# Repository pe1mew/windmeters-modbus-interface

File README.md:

# Windmeters Modbus Interface

A CH32V003-based interface board that bridges classic analog wind sensors —
a **cup anemometer** (reed-relay pulses) and a **wind-vane potentiometer**
(0–360°) — onto **Modbus RTU over RS-485**, powered by 24 V passive PoE and
designed for daisy-chained field buses.

One PCB serves both sensor types; the firmware build selects the variant.
Each variant responds at its own Modbus address, selected by a solder
jumper:

| Variant | Jumper open | Jumper bridged |
|---|---|---|
| Wind speed (`wind_speed`) | **30** | 35 |
| Wind direction (`wind_direction`) | **31** | 36 |
| Both, one slave (`wind_combined`) | **32** | 37 |

The `wind_combined` build serves both sensors through a single Modbus
address; its register map carries speed and direction at their own
register addresses, with the direction raw-ADC diagnostic at 30013 (30005
holds the speed pulse count).

## Project status (2026-07)

| Area | State |
|---|---|
| Requirements | [`design/TDS.md`](design/TDS.md) **v0.9** — 69 active requirements (incl. FR-S39 persistence, FR-S40 runtime calibration) + §4 as-built hardware from the KiCad PCB, hardened by multi-agent audits + verification passes |
| Drivers | Pulse counting, ADC/circular-mean, Modbus RTU — all HIL-verified on silicon ([`design/driverDevelopment.md`](design/driverDevelopment.md)) |
| Product firmware | Integration stages A–F complete; **TDS-functionally complete** on all three variants (speed, direction, combined), acceptance suite green ([`design/integrationPlan.md`](design/integrationPlan.md)) |
| Hardware/HIL | KiCad schematic/PCB in design; **§9.1 MAX3485-rig HIL complete on all three variants**; real-PCB rows (§9.2) pending |
| Release | Firmware version 1 not yet tagged ([`software/firmware/RELEASES.md`](software/firmware/RELEASES.md)) |

## Hardware

- **MCU**: WCH CH32V003J4M6 (RISC-V, SOP-8, 16 KB flash / 2 KB RAM) — the
  8-pin package drives the whole design: single-wire UART discipline,
  remap tricks, and a zero-interrupt firmware architecture
  ([`design/softwareArchitecture.md`](design/softwareArchitecture.md)).
- **RS-485**: MAX3485; DI+RO tied to PD6, DE+R̄Ē tied to PC2 with a 10 k
  pull-down (keeps the bus safe during reset/flashing); 120 Ω terminator
  behind a solder jumper; A/B fail-safe bias; SM712 TVS.
- **Power**: 24 V passive PoE on the spare pairs (4/5 = +, 7/8 = −) →
  DB207 bridge (polarity protection only) → HLK-K7803 buck → 3.3 V.
- **Connectors**: 2× RJ45 for the daisy-chained bus, two RJ14 sensor jacks
  (anemometer + wind direction), 3-pin header for the WCH-LinkE programmer
  (SWIO on PD1).

## Modbus register map (summary)

12 input registers (FC04) and 6 holding registers (FC03/06/16); registers
of an absent sensor read 0, and the combined build adds a 13th input
register (30013, direction raw ADC). Highlights: instantaneous and averaged
values, status bits, identification (build + firmware version), uptime,
CRC/served counters, gust, seconds-since-last-pulse.
**6** holding registers: direction offset, measurement window, averaging
window, low-speed cut-off, and the anemometer calibration (factor C +
pulses-per-rotation, FR-S40 — so one image serves any anemometer, set over
Modbus). All **persisted in flash across reset/power-loss** (FR-S39); the §2.8
defaults apply only on first boot / erased store. The authoritative map with
ranges, defaults, and requirement IDs is [`design/TDS.md`](design/TDS.md)
§2.7/§2.8.

## Repository layout

| Path | Contents |
|---|---|
| [`design/`](design/README.md) | The design-document chain (index in [`design/README.md`](design/README.md)): scratchBook → TDS → softwareArchitecture (+ UML diagrams in `design/diagrams/`) → driverDevelopment → integrationPlan |
| `hardware/KiCad/` | Schematic + PCB (KiCad); symbol libraries as git submodules |
| `hardware/Documentation/` | Component datasheets (HLK-K78xx, DB20x, Kradex enclosure, …) |
| `software/firmware/` | Product firmware (PlatformIO + ch32v003fun), three build envs (speed / direction / combined) + `_test` variants |
| `software/drivers/` | Standalone driver projects with HIL test shells (the verified libraries the product references in place) |
| `software/hil/` | Scripted hardware-in-the-loop harness: Saleae Logic 2 (MCP) + ADALM2000 (libm2k) + `acceptance/` pytest suite; consolidated [`testReport.md`](software/hil/testReport.md) |
| `Doxyfile` | Doxygen config — builds a single site (design docs + API reference) with this README as the landing page |
| `documentation/` | Chip pinout and project reference images |

Clone with submodules:

```sh
git clone --recurse-submodules https://github.com/pe1mew/windmeters-modbus-interface.git
```

## Building and flashing

Requires [PlatformIO](https://platformio.org/) and a WCH-LinkE on SWIO.

```sh
cd software/firmware
pio run -e wind_speed              # or wind_direction, or wind_combined
pio run -e wind_speed -t upload    # flash via WCH-LinkE
```

Resource ceilings (14 336 B flash / 1 792 B RAM, NFR-RES01) are enforced as
hard build gates. `*_test` environments add bench-only hooks — never
release those binaries. The firmware version byte lives in
`src/version.h`; the release process is documented in `RELEASES.md`.

## Testing

- **Host tests** (no hardware): the circular-mean math is exhaustively
  verified in Python — `python software/drivers/common/circmean/test_circmean.py`.
- **Acceptance suite** (bench: Saleae Logic 2 with its MCP server, ADALM2000,
  WCH-LinkE, TTL Modbus rig):

  ```sh
  cd software/hil/acceptance
  ..\.venv-m2k\Scripts\python.exe -m pytest . --build speed
  ```

  One command per flashed variant; covers the register map, protocol
  vectors, measurement services, averaging engine, version chain, and
  build gates. See [`software/hil/README.md`](software/hil/README.md) for
  instrument setup, wiring, and the bench-quirk catalogue.
- **HIL test report** — [`software/hil/testReport.md`](software/hil/testReport.md)
  consolidates every hardware-in-the-loop test (driver-phase, integration-
  stage, and MAX3485 transceiver rig) with its setup, expected result, and
  pass/fail verdict in one place.

## Documentation

- **Design record** — [`design/README.md`](design/README.md) indexes the
  document chain (requirements → architecture → drivers → integration) and
  the UML diagrams.
- **API + design site** — the firmware headers/sources carry full Doxygen,
  and [`Doxyfile`](Doxyfile) folds the design docs in as pages with this
  README as the landing page. Build the browsable HTML with:

  ```sh
  doxygen Doxyfile        # output in documentation/doxygen/html/index.html
  ```
- **Test evidence** — [`software/hil/testReport.md`](software/hil/testReport.md)
  is the consolidated hardware-in-the-loop test report.

## Related repositories

- [`pe1mew/windmeters-modbus-interface-tester`](https://github.com/pe1mew/windmeters-modbus-interface-tester) —
  the Modbus RTU master bench tool (M5Stack AtomS3 + RS-485) used to
  exercise this device; its bench findings seeded this project's TDS.

## License

Software is provided under a Source-Available Non-Commercial License;
documentation and images under CC BY-NC-ND 4.0. See [LICENSE](LICENSE) and
[license.md](license.md). Third-party datasheets and KiCad library
submodules remain under their owners' terms.

## Author

Remko Welling (PE1MEW)

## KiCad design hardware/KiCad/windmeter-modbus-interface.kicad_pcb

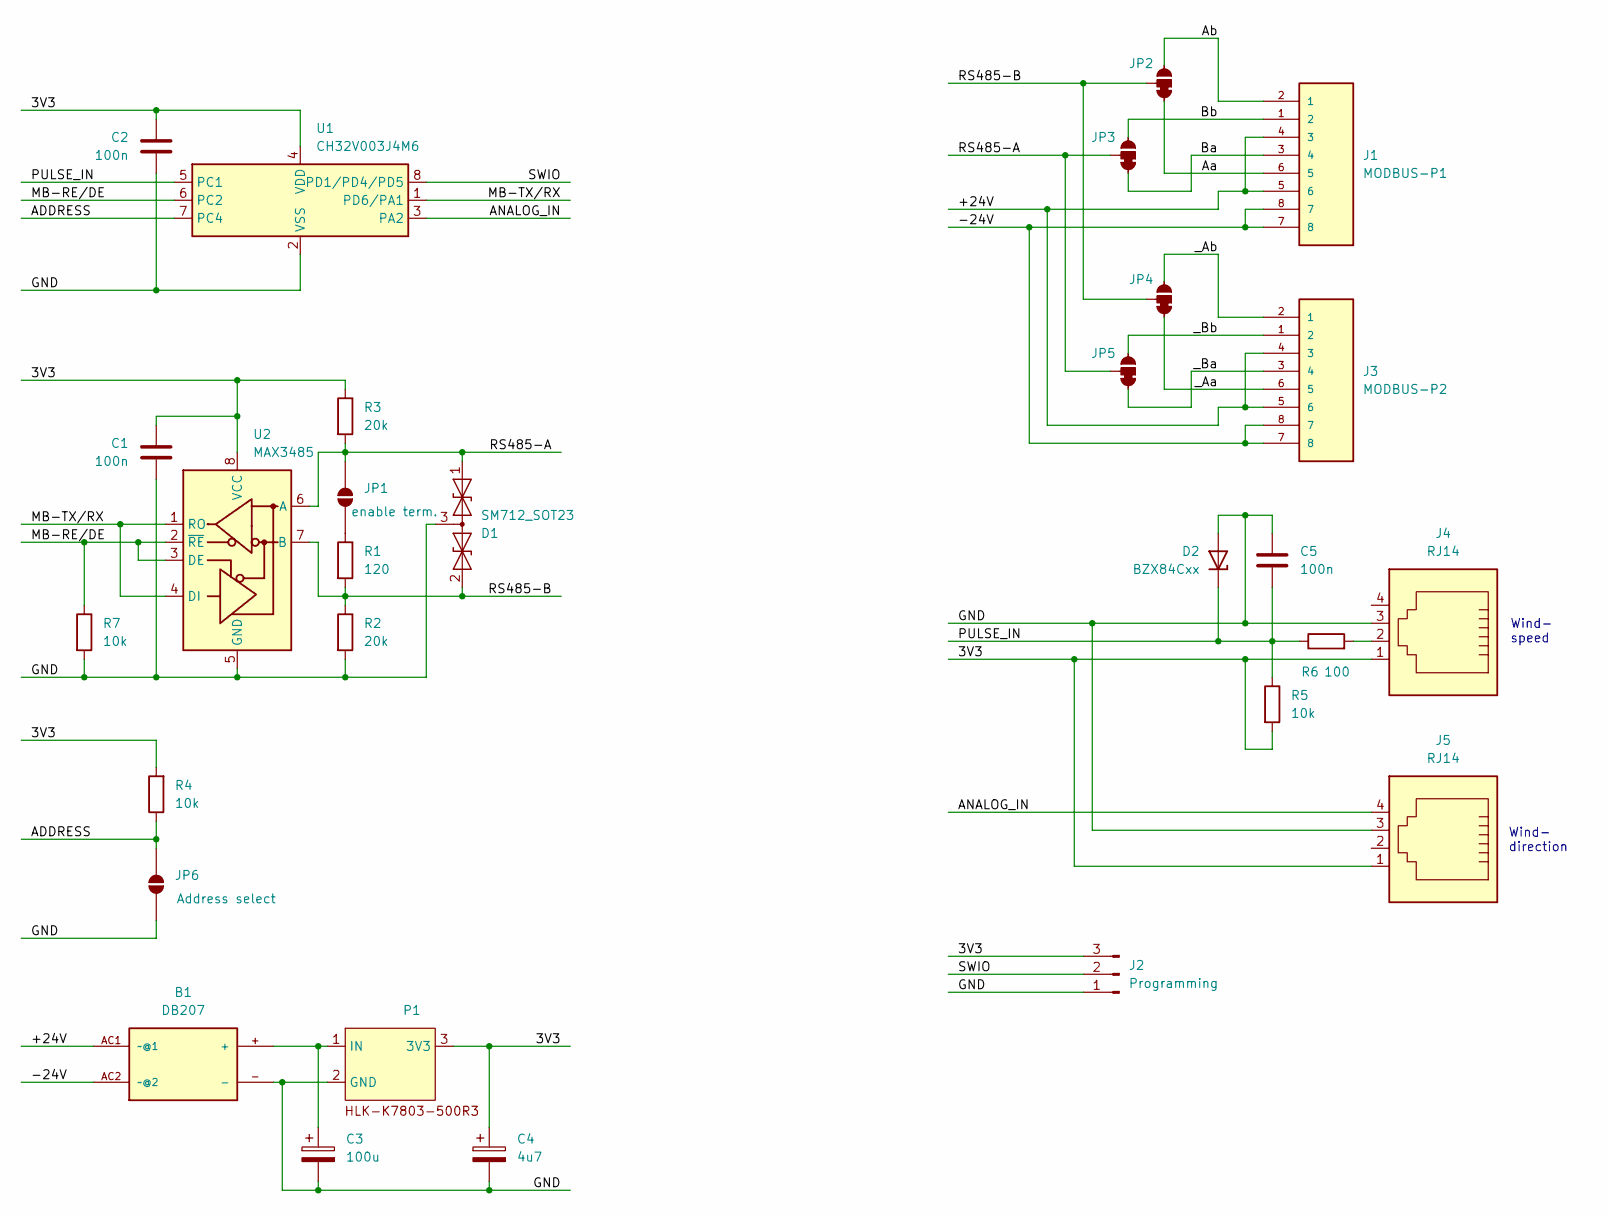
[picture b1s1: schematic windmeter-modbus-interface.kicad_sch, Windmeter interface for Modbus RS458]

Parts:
B1: DB207; DB207-DIP-4
C1, C2, C5: 100n; C_1206_3216Metric_Pad1.33x1.80mm_HandSolder
C3: 100u; CP_Radial_D8.0mm_P5.00mm
C4: 4u7; CP_Radial_D5.0mm_P2.50mm
D1: SM712_SOT23; SOT-23
D2: BZX84Cxx; SOT-23
J1: MODBUS-P1; CONN_215877-1; PARTREV AF1
J2: Programming; PinHeader_1x03_P2.54mm_Vertical
J3: MODBUS-P2; CONN_215877-1; PARTREV AF1
J4, J5: RJ14; RJ14_Connfly_DS1133-S4_Horizontal
JP1: enable term.; SolderJumper-2_P1.3mm_Open_Pad1.0x1.5mm
JP2, JP3, JP4, JP5: SolderJumper-3_P1.3mm_Bridged12_Pad1.0x1.5mm_NumberLabels
JP6: Address select; SolderJumper-2_P1.3mm_Open_Pad1.0x1.5mm
P1: HLK-K7803-500R3
R1: 120; R_1206_3216Metric_Pad1.30x1.75mm_HandSolder
R2, R3: 20k; R_1206_3216Metric_Pad1.30x1.75mm_HandSolder
R4, R5, R7: 10k; R_1206_3216Metric_Pad1.30x1.75mm_HandSolder
R6: 100; R_1206_3216Metric_Pad1.30x1.75mm_HandSolder
U1: CH32V003J4M6; JEITA_SOIC-8_3.9x4.9mm_P1.27mm
U2: MAX3485; SOIC-8_3.9x4.9mm_P1.27mm

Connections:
/3V3: C1.1, C2.1, C4.1, J2.3, J4.1, J5.1, P1.3 (3V3), R3.1, R4.2, R5.2, U1.4 (VDD), U2.8 (VCC)
/+24V: B1.AC1 (~@1), J1.4 (3), J1.5 (6), J3.4 (3), J3.5 (6)
/-24V: B1.AC2 (~@2), J1.7 (8), J1.8 (7), J3.7 (8), J3.8 (7)
/ADDRESS: JP6.2 (B), R4.1, U1.7 (PC4)
/ANALOG_IN: J5.4, U1.3 (PA2)
/Aa: J1.6 (5), JP2.1 (A)
/Ab: J1.2 (1), JP2.3 (C)
/Ba: J1.3 (4), JP3.1 (A)
/Bb: J1.1 (2), JP3.3 (C)
/GND: B1.-, C1.2, C2.2, C3.2, C4.2, C5.1, D1.3 (common), D2.1 (A), J2.1, J4.3, J5.3, JP6.1 (A), P1.2 (GND), R2.2, R7.2, U1.2 (VSS), U2.5 (GND)
/MB-RE/DE: R7.1, U1.6 (PC2), U2.2 (~RE), U2.3 (DE)
/MB-TX/RX: U1.1 (PD6/PA1), U2.1 (RO), U2.4 (DI)
/PULSE_IN: C5.2, D2.3 (K), R5.1, R6.1, U1.5 (PC1)
/RS485-A: D1.1 (A1), JP1.2 (B), JP3.2 (B), JP5.2 (B), R3.2, U2.6 (A)
/RS485-B: D1.2 (A2), JP2.2 (B), JP4.2 (B), R1.2, R2.1, U2.7 (B)
/SWIO: J2.2, U1.8 (PD1/PD4/PD5)
/_Aa: J3.6 (5), JP4.1 (A)
/_Ab: J3.2 (1), JP4.3 (C)
/_Ba: J3.3 (4), JP5.1 (A)
/_Bb: J3.1 (2), JP5.3 (C)
unnamed: J4.2, R6.2
unnamed: JP1.1 (A), R1.1
unnamed: B1.+, C3.1, P1.1 (IN)

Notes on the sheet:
Wind- speed
Wind- direction

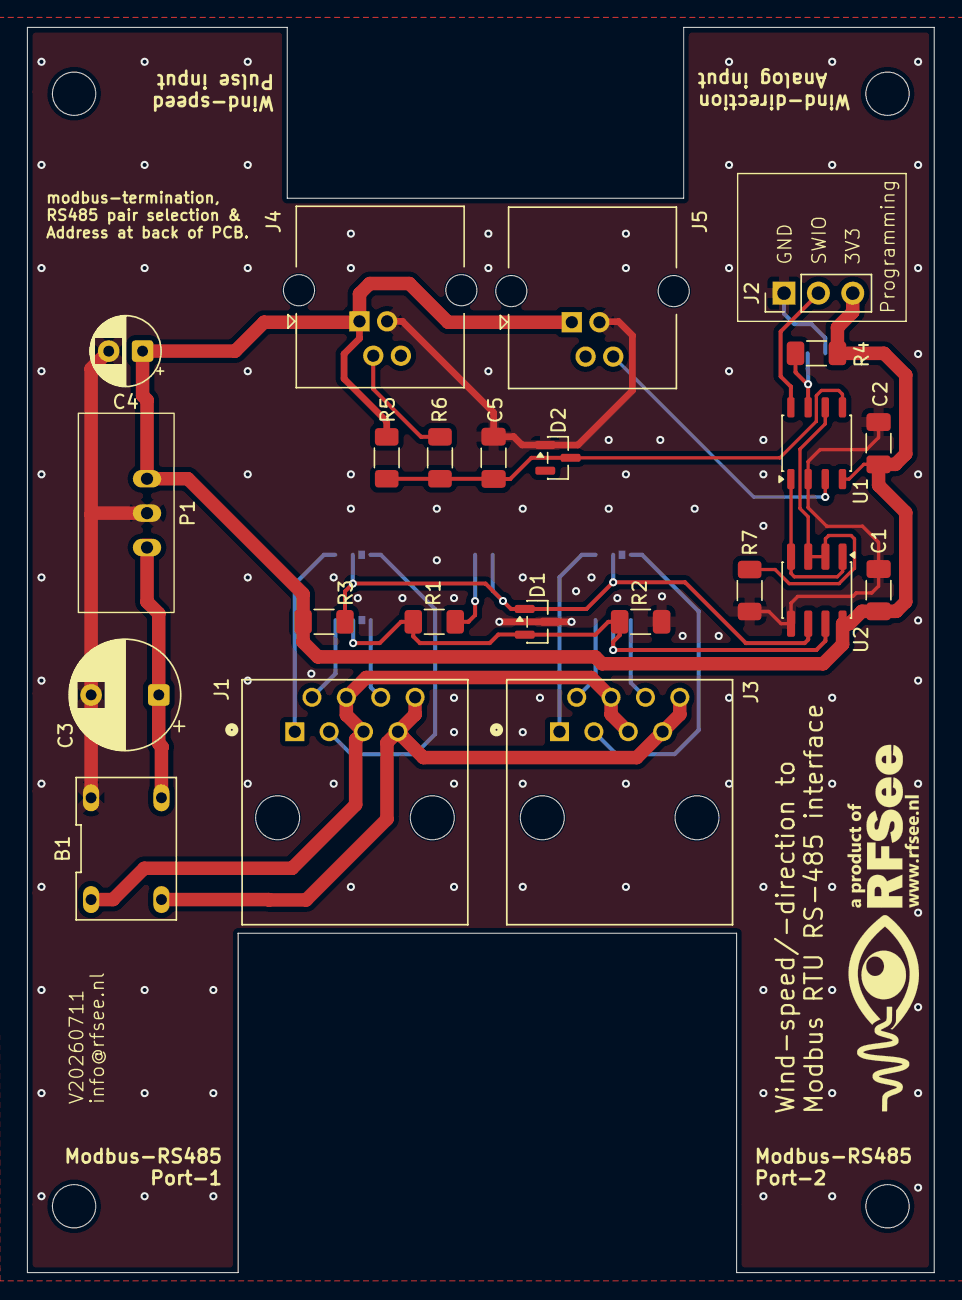
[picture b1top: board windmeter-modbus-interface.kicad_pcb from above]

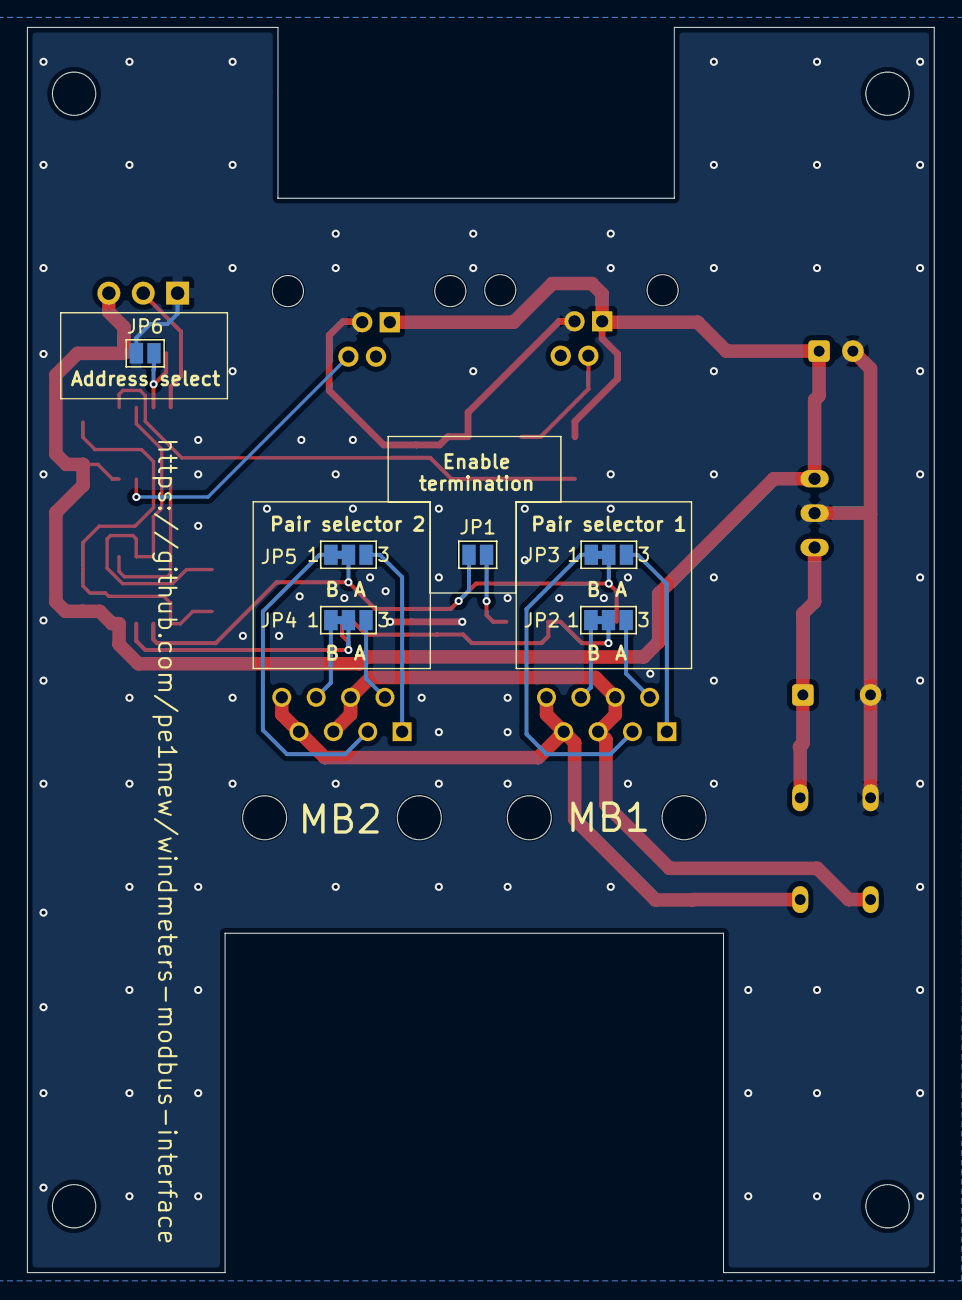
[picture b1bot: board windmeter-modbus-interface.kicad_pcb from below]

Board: 2 copper layers, 67.0 x 92.0 mm, 29 parts (6 on the bottom side), 23 nets.

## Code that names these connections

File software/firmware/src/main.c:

/*
 * Windmeter Modbus interface — product firmware (CH32V003J4M6, SOIC-8)
 *
 * Zero-ISR cooperative super-loop (design/softwareArchitecture.md).
 * Stage D state (design/integrationPlan.md): full register image (regs.c)
 * + real measurement services (meas_speed.c / meas_dir.c). The averaging
 * engine (30003/30004/30012 + warm-up semantics) is stage E.
 *
 * Pin assignment: design/scratchBook.md — PD6 Modbus line (remap-switching
 * discipline, no HDSEL), PC2 DE/R̄Ē, PA2 wind-direction ADC, PC1 anemometer
 * pulses, PC4 address jumper, PD1 SWIO.
 */

#include "sensors.h" /* variant selection -> HAVE_WIND_SPEED/DIRECTION */
#include "board.h"
#include "ch32fun.h"
#include "mb.h"
#include "meas.h"
#include "regs.h"

#ifdef HAVE_WIND_SPEED
#include "ws.h"
#endif
#ifdef HAVE_WIND_DIRECTION
#include "wd.h"
#endif

int main(void)
{
	SystemInit();
	funGpioInitAll();

	/* FR-S18 init order:
	 * (1) PC2/DE low first + (2) PC4 address latch + IWDG + PVD ... */
	board_init_early();
	/* (3) sensor front-end(s) ready — a combined build inits both. */
#ifdef HAVE_WIND_SPEED
	ws_init();
#endif
#ifdef HAVE_WIND_DIRECTION
	wd_init(); /* includes ADC self-calibration */
#endif
	/* regs_init loads the persisted holdings (FR-S39) BEFORE the
	 * measurement services latch the window, so the first window already
	 * uses the stored duration — no spurious first-window abort at boot. */
	regs_init(board_mb_address());
#ifdef HAVE_WIND_SPEED
	meas_speed_init();
#endif
#ifdef HAVE_WIND_DIRECTION
	meas_dir_init();
#endif
	/* (4) USART receiver enabled last. */
	mb_init(regs_cfg());

	const uint32_t second_ticks = FUNCONF_SYSTEM_CORE_CLOCK;
	uint32_t t_second = SysTick->CNT;

	while (1)
	{
		mb_poll();
		regs_service(); /* FR-S30: 40002/40003 change -> accumulator clear */
		regs_persist_service(); /* FR-S39: save changed settings to flash
		                         * (after mb_poll sent any response) */
#ifdef HAVE_WIND_SPEED
		meas_speed_service();
#endif
#ifdef HAVE_WIND_DIRECTION
		meas_dir_service();
#endif

		if ((uint32_t)(SysTick->CNT - t_second) >= second_ticks)
		{
			t_second += second_ticks;
			regs_second_tick();
		}

#ifdef TEST_HOOKS
		if (regs_test_hang_requested())
			for (;;)
				; /* FR-S20 test: stop servicing AND feeding — dog bites */
#endif
		/* FR-S20: refresh only here, at the end of a full loop pass, and
		 * only while the rail is healthy (FR-S22). */
		if (board_power_ok())
			board_iwdg_feed();
	}
}

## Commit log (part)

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2026-06-22 commit again
2026-06-22 Update PCB
2026-06-27 Added power circuit
2026-06-28 First scaffolding
